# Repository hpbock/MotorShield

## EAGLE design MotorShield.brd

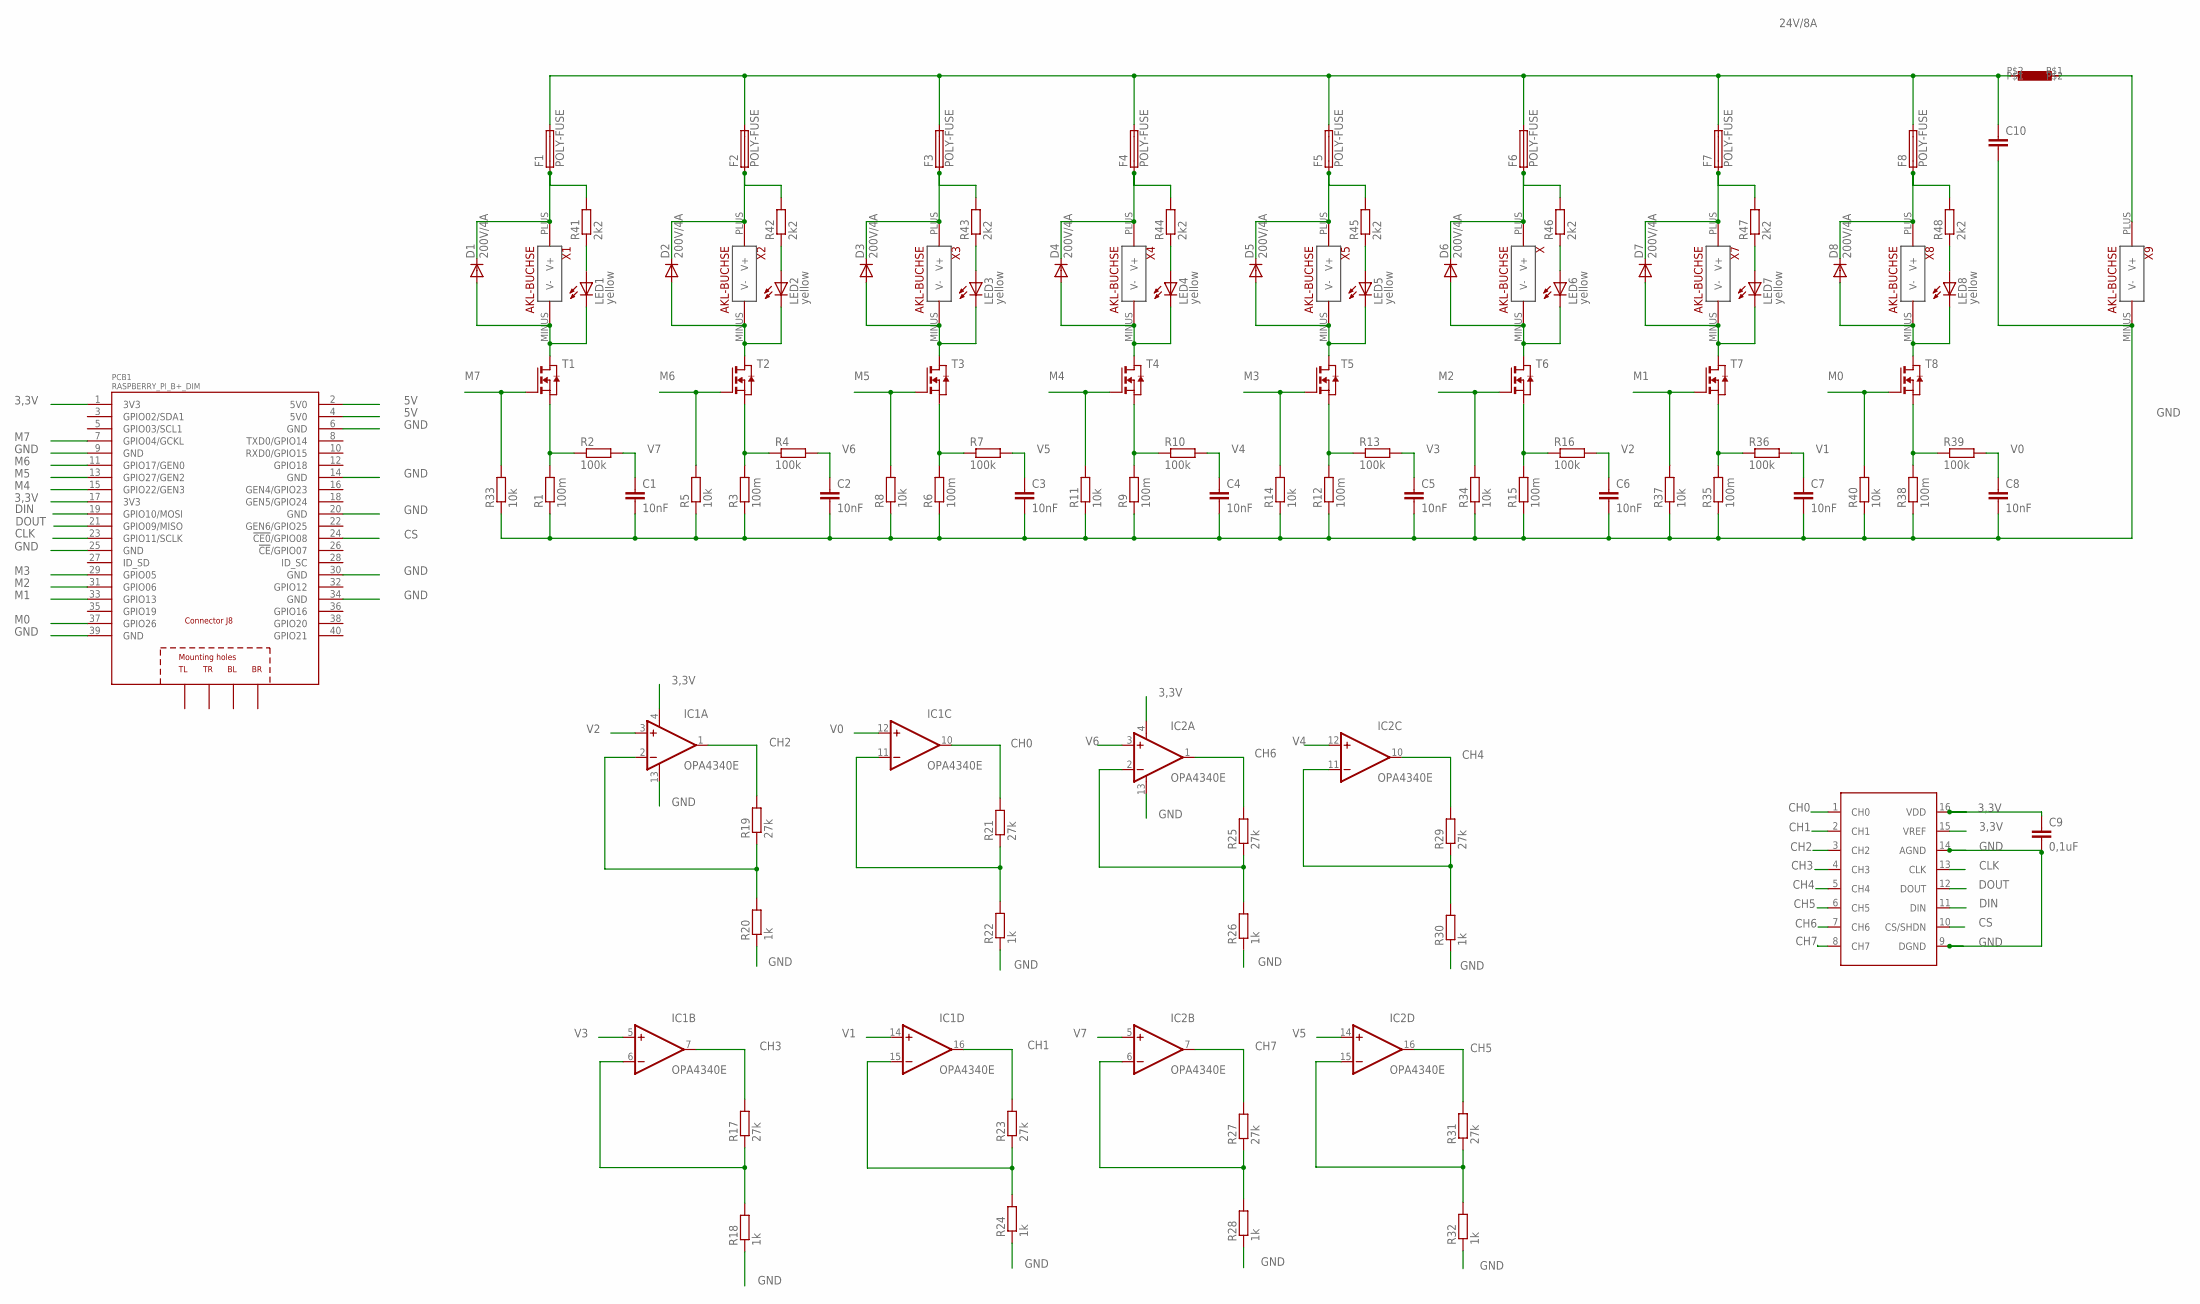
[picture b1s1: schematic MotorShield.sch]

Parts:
C1, C2, C3, C4, C5, C6, C7, C8: 10nF; C0805
C9: 0,1uF; C0805
C10: C-EUC1812; C1812
D1, D2, D3, D4, D5, D6, D7, D8: 200V/4A; DO214AA
F1, F2, F3, F4, F5, F6, F7, F8: POLY-FUSE; 1812L050
IC1, IC2: OPA4340E; SSOP16BU
IC3: MCP3008SO16; SO16
L1: MPI4040; 4040
LED1, LED2, LED3, LED4, LED5, LED6, LED7, LED8: yellow; CHIP-LED0603
PCB1: RASPBERRY_PI_B+_DIM; RASPBERRY_PI_BPLUS_DIM
R1, R3, R6, R9, R12, R15, R35, R38: 100m; R0805
R2, R4, R7, R10, R13, R16, R36, R39: 100k; R0805
R5, R8, R11, R14, R33, R34, R37, R40: 10k; R0805
R17, R19, R21, R23, R25, R27, R29, R31: 27k; R0805
R18, R20, R22, R24, R26, R28, R30, R32: 1k; R0805
R41, R42, R43, R44, R45, R46, R47, R48: 2k2; R0603
T1, T2, T3, T4, T5, T6, T7, T8: NMOSSOT23; SOT-23
X, X1, X2, X3, X4, X5, X7, X8, X9: AKL-BUCHSE

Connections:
3,3V: C9.1, IC1.4 (V+), IC2.4 (V+), IC3.15 (VREF), IC3.16 (VDD), PCB1.1 (3V3), PCB1.17 (3V3)
5V: PCB1.2 (5V0), PCB1.4 (5V0)
24V/1A: D1.C, F1.P$1 (1), R41.2, X1.PLUS (V+)
24V/8A: C10.1, F1.P$2 (2), F2.P$2 (2), F3.P$2 (2), F4.P$2 (2), F5.P$2 (2), F6.P$2 (2), F7.P$2 (2), F8.P$2 (2), L1.P$2
CH0: IC1.10 (OUT), IC3.1 (CH0), R21.2
CH1: IC1.16 (OUT), IC3.2 (CH1), R23.2
CH2: IC1.1 (OUT), IC3.3 (CH2), R19.2
CH3: IC1.7 (OUT), IC3.4 (CH3), R17.2
CH4: IC2.10 (OUT), IC3.5 (CH4), R29.2
CH5: IC2.16 (OUT), IC3.6 (CH5), R31.2
CH6: IC2.1 (OUT), IC3.7 (CH6), R25.2
CH7: IC2.7 (OUT), IC3.8 (CH7), R27.2
CLK: IC3.13 (CLK), PCB1.23 (GPIO11/SCLK)
CS: IC3.10 (CS/SHDN), PCB1.24 (!CE0!/GPIO08)
DIN: IC3.11 (DIN), PCB1.19 (GPIO10/MOSI)
DOUT: IC3.12 (DOUT), PCB1.21 (GPIO09/MISO)
GND: C1.2, C2.2, C3.2, C4.2, C5.2, C6.2, C7.2, C8.2, C9.2, C10.2, IC1.13 (V-), IC2.13 (V-), IC3.9 (DGND), IC3.14 (AGND), PCB1.6 (GND), PCB1.9 (GND), PCB1.14 (GND), PCB1.20 (GND), PCB1.25 (GND), PCB1.30 (GND), PCB1.34 (GND), PCB1.39 (GND), R1.1, R3.1, R5.1, R6.1, R8.1, R9.1, R11.1, R12.1, R14.1, R15.1, R18.1, R20.1, R22.1, R24.1, R26.1, R28.1, R30.1, R32.1, R33.1, R34.1, R35.1, R37.1, R38.1, R40.1, X9.MINUS (V-)
M0: PCB1.37 (GPIO26), R40.2, T8.3 (G)
M1: PCB1.33 (GPIO13), R37.2, T7.3 (G)
M2: PCB1.31 (GPIO06), R34.2, T6.3 (G)
M3: PCB1.29 (GPIO05), R14.2, T5.3 (G)
M4: PCB1.15 (GPIO22/GEN3), R11.2, T4.3 (G)
M5: PCB1.13 (GPIO27/GEN2), R8.2, T3.3 (G)
M6: PCB1.11 (GPIO17/GEN0), R5.2, T2.3 (G)
M7: PCB1.7 (GPIO04/GCKL), R33.2, T1.3 (G)
unnamed: D1.A, LED1.C, T1.1 (D), X1.MINUS (V-)
unnamed: R1.2, R2.1, T1.2 (S)
unnamed: D8.C, F8.P$1 (1), R48.2, X8.PLUS (V+)
unnamed: D7.C, F7.P$1 (1), R47.2, X7.PLUS (V+)
unnamed: IC1.2 (-IN), R19.1, R20.2
unnamed: D6.C, F6.P$1 (1), R46.2, X.PLUS (V+)
unnamed: D5.C, F5.P$1 (1), R45.2, X5.PLUS (V+)
unnamed: D4.C, F4.P$1 (1), R44.2, X4.PLUS (V+)
unnamed: D2.A, LED2.C, T2.1 (D), X2.MINUS (V-)
unnamed: R3.2, R4.1, T2.2 (S)
unnamed: D3.C, F3.P$1 (1), R43.2, X3.PLUS (V+)
unnamed: D2.C, F2.P$1 (1), R42.2, X2.PLUS (V+)
unnamed: IC1.6 (-IN), R17.1, R18.2
unnamed: LED1.A, R41.1
unnamed: D3.A, LED3.C, T3.1 (D), X3.MINUS (V-)
unnamed: R6.2, R7.1, T3.2 (S)
unnamed: LED2.A, R42.1
unnamed: LED3.A, R43.1
unnamed: LED5.A, R45.1
unnamed: IC1.11 (-IN), R21.1, R22.2
unnamed: LED4.A, R44.1
unnamed: LED6.A, R46.1
unnamed: LED7.A, R47.1
unnamed: D4.A, LED4.C, T4.1 (D), X4.MINUS (V-)
unnamed: IC1.15 (-IN), R23.1, R24.2
unnamed: L1.P$1, X9.PLUS (V+)
unnamed: R9.2, R10.1, T4.2 (S)
unnamed: LED8.A, R48.1
unnamed: IC2.2 (-IN), R25.1, R26.2
unnamed: IC2.6 (-IN), R27.1, R28.2
unnamed: IC2.11 (-IN), R29.1, R30.2
unnamed: D5.A, LED5.C, T5.1 (D), X5.MINUS (V-)
unnamed: R12.2, R13.1, T5.2 (S)
unnamed: IC2.15 (-IN), R31.1, R32.2
unnamed: D6.A, LED6.C, T6.1 (D), X.MINUS (V-)
unnamed: R15.2, R16.1, T6.2 (S)
unnamed: D7.A, LED7.C, T7.1 (D), X7.MINUS (V-)
unnamed: R35.2, R36.1, T7.2 (S)
unnamed: D8.A, LED8.C, T8.1 (D), X8.MINUS (V-)
unnamed: R38.2, R39.1, T8.2 (S)
V0: C8.1, IC1.12 (+IN), R39.2
V1: C7.1, IC1.14 (+IN), R36.2
V2: C6.1, IC1.3 (+IN), R16.2
V3: C5.1, IC1.5 (+IN), R13.2
V4: C4.1, IC2.12 (+IN), R10.2
V5: C3.1, IC2.14 (+IN), R7.2
V6: C2.1, IC2.3 (+IN), R4.2
V7: C1.1, IC2.5 (+IN), R2.2

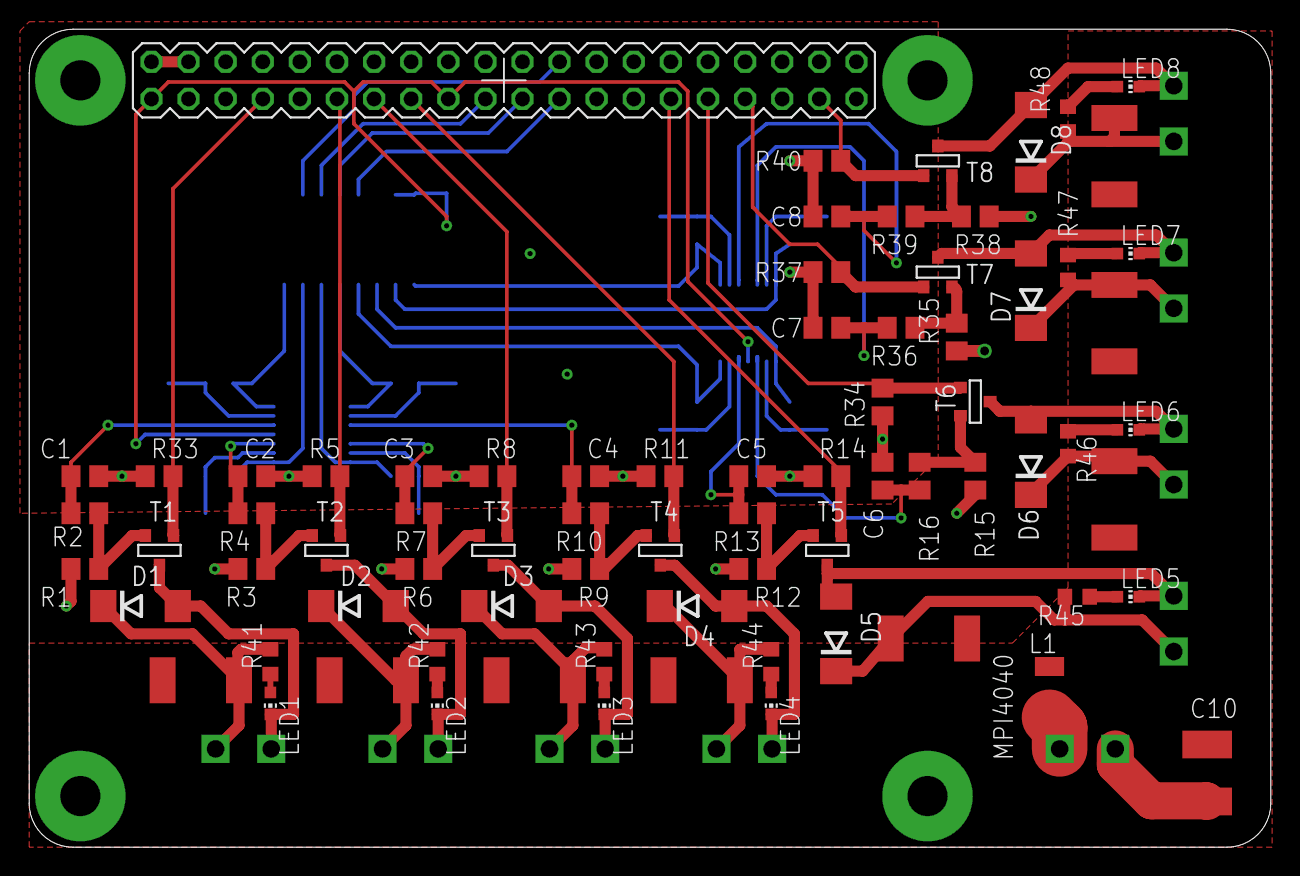
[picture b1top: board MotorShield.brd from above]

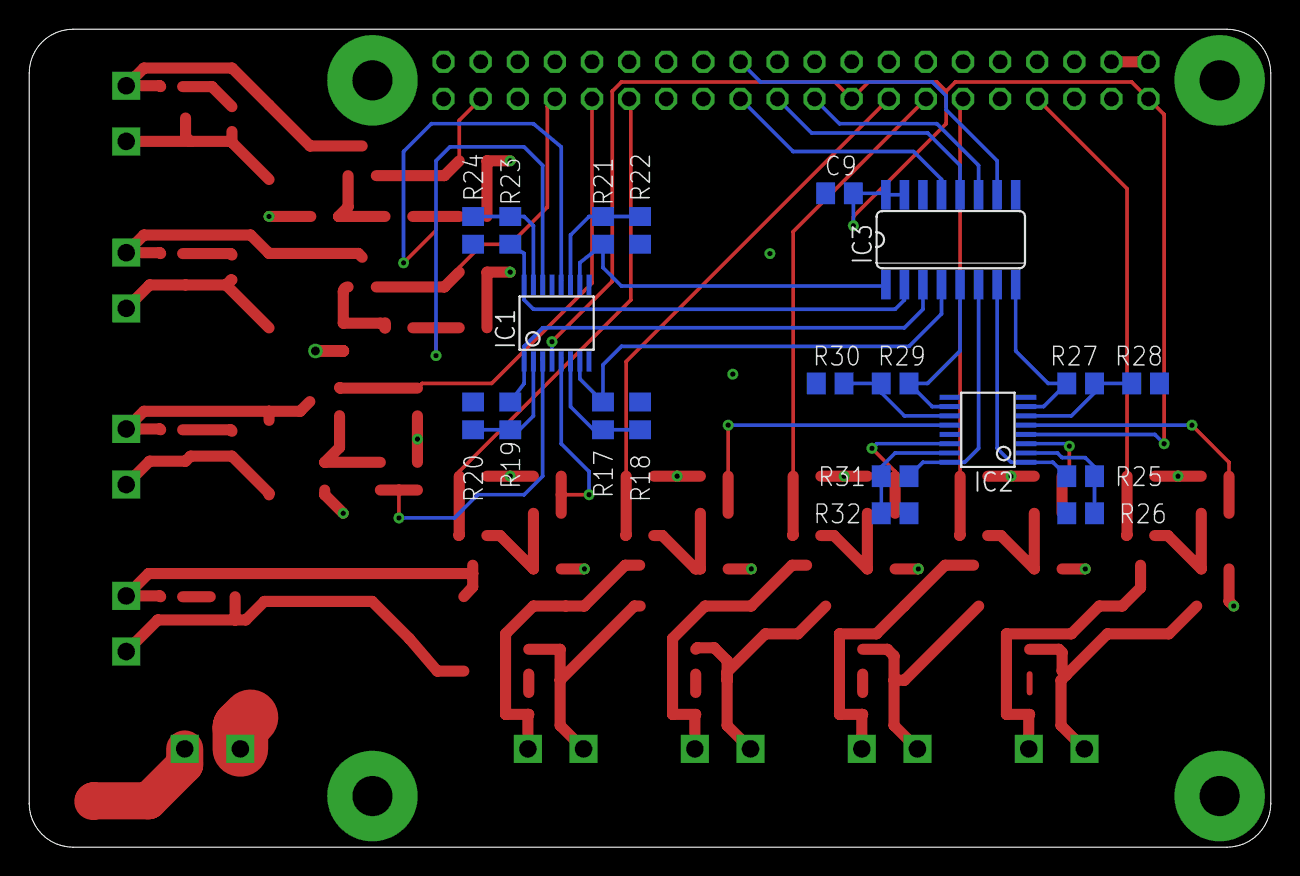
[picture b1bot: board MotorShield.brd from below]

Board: 2 copper layers, 85.0 x 56.0 mm, 104 parts (20 on the bottom side), 73 nets.

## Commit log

2017-09-22 named connector blocks and ADC
2017-09-22 added LEDs that signalize active output to close IUNO-TDM/MotorShield#6
